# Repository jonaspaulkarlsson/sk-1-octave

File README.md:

# sk-1-octave
## Octave switch for the Casio SK-1 keyboard

## Background
The SK-1 is a great keyboard, but it's range is limited due to the short 2.5 octave keyboard.

Looking at the schematic in the service manual (http://www.burnkit2600.com/manuals/CASIO_SK-1_SRVC.pdf), the clock for the microprocessor is generated by a simple LC oscillator, like what is presented here: http://www.learningaboutelectronics.com/Articles/Colpitts-oscillator-calculator.php.

The tuning of the instrument is controlled by a variable capacitor, which controls the frequency of the LC clock oscillator. The idea is to replace the inverter in the original oscillator with a CMOS inverter IC, add a clock divider to drop the frequency by four (down two octaves) and a multiplexer to select either the original or the divided frequency.

PCB area around the micro processor and LC oscillator circuit:

Original oscillator input signal:

Original oscillator output signal:

## Circuit design
The schematic and PCB was designed in KiCad.

The schematic below shows the circuit:

The oscillator core consists of the existing inductor and capacitors from the original circuit, but now connected to one part of U1, a 4069 hex CMOS inverter. The signal from the oscillator is divided by four by two stages from U2, a dual D flip-flop. Lastly, one of the original or divided down signals are selected by one channel of U3, a quad mux. The select input of the mux is connected to a switch that selects either the original frequency when the switch is closed, or the divided down frequency when the switch is open.

The R2, R3, R4 and C1 network scales the output to roughly the same voltage range as the original clock signal. This is probably not necessary but the circuit was included just to be safe. In the end, C1 was excluded.

The PCB is shown in the picture below:

All connections are made to test points around the edges for easy soldering.

## Installation
1. Open upp the case and place both halves upside down, exposing the main PCB.
2. Mount the octave switch PCB with double sided tape, hot glue or whatever you have at hand in the position shown in the picture 
3. Cut the traces going to the processor where indicated by the red lines in the picture, and scrape off the solder resist on the one going in under the corner of the IC: 
4. Solder wires to the octave switch PCB from the solder joints on the SK-1 PCB as shown in the picture. Solder in the OUT signal with as thin a wire as possible to minimize stress on the cut wire. Take care to leave the area close to the tuning inductor free from wires. 
5. Mount a toggle swithch to some convenient place in the case, probaly the empty space next to the speaker is most convenient. Connect the switch with long twisted wires to the SW1 and SW2 pads. 
6. Put your SK-1 back together and enjoy your extended note range!

It should be noted that the SK-1 uses a weird form of negative logic, so what is connected to GND the octave switch PCB is actually the negative supply rail, and what is connected to +5V is ground. What matters in the end is that both PCBs sees signals that are in the correct voltage ranges for their respective supplies.

## Results
Audio demos at [Soundcloud](https://soundcloud.com/exterm/sk-1-octave)

The circuit works well and unlocks some of the potential of this instrument. I really like the cruncy atmospheric sound of the lower octaves.

However there are some side effects (features?) due to the nature of this hack. Since the clock speed for the whole system is slowed down, _everything_ slows down. Rythms (nice and crunchy, but slow), portamento, vibrato, envelopes etc. It doesn't bother me too much, but it should be noted that the integration is not seamless.

## Retrospective
1. I thought I ordered 1mm thick PCBs, but apparently it was the standard 1.6mm. I wanted to keep as much clearance to the case as possible, not knowing exactly how much room there was, but 1.6mm worked out fine.
2. The black solder resist fom JLCPCB was quite fragile and chipped away in one place. I will go for the standard green in the future.
3. It would have been cool to design the PCB around the solder in poisitions on the SK-1 PCB so that it could be attached directly with castellated edges. It would have been a fun exercise. Maybe for another project.
4. Yes I know the soldering looks awful, I should probably redo it, but... meh.
5. The SK-1 PCB is covered in sticky flux. I did clean it up around the area where I attached the octave switch PCB, but yeah, I know it looks nasty.

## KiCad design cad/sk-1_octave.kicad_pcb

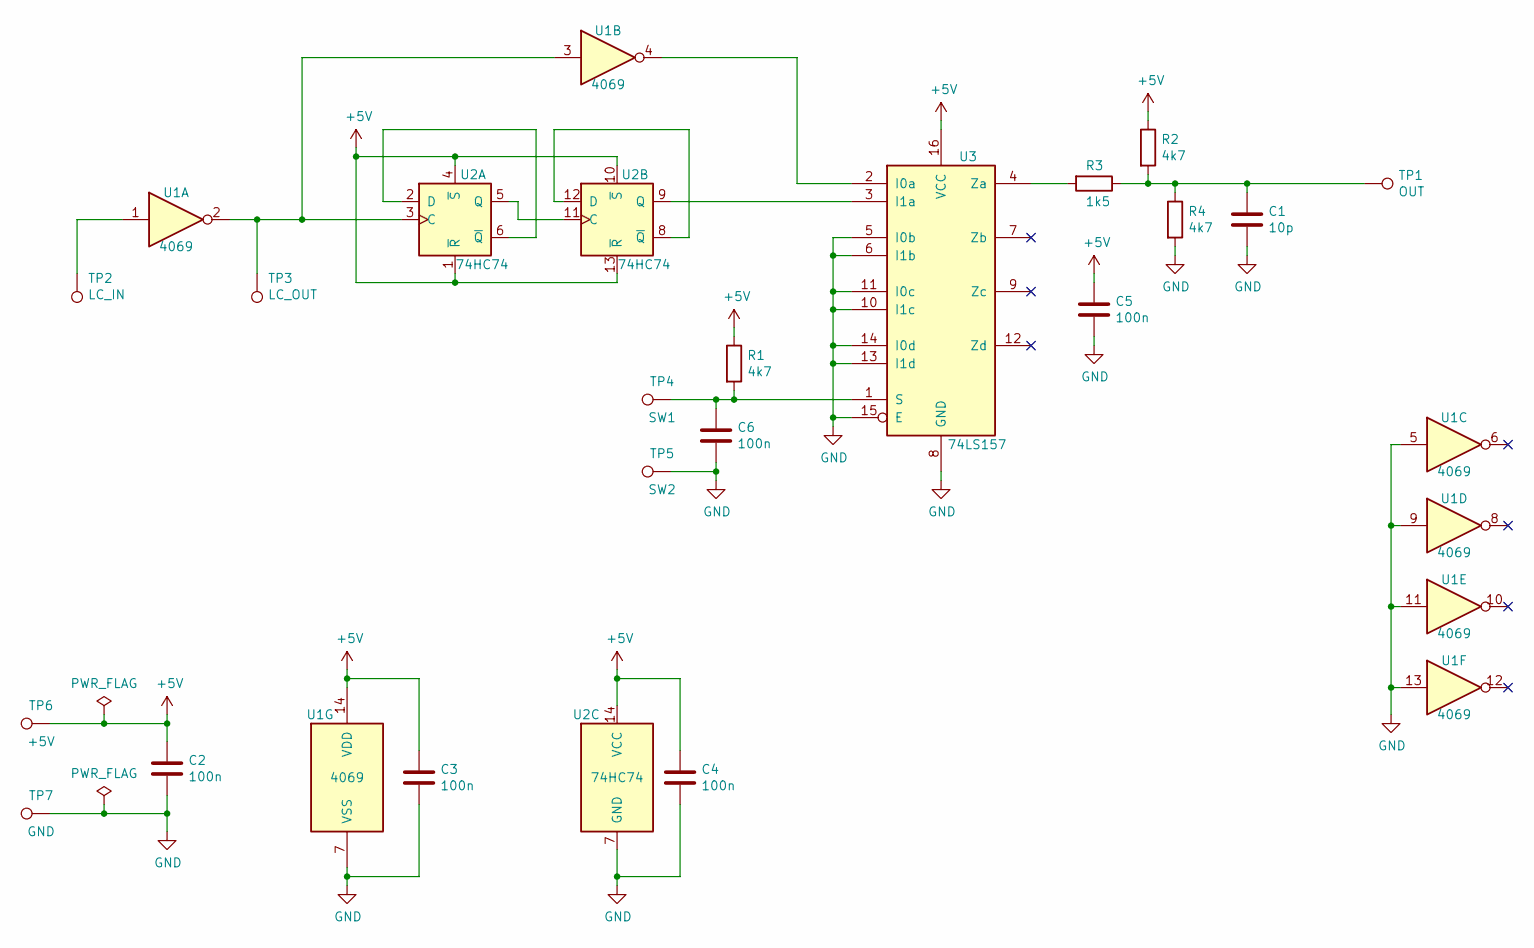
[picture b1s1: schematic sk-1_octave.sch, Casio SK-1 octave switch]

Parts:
C1: 10p; C_0603_1608Metric_Pad1.08x0.95mm_HandSolder
C2, C3, C4, C5, C6: 100n; C_0603_1608Metric_Pad1.08x0.95mm_HandSolder
R1, R2, R4: 4k7; R_0603_1608Metric_Pad0.98x0.95mm_HandSolder
R3: 1k5; R_0603_1608Metric_Pad0.98x0.95mm_HandSolder
TP1: OUT; TestPoint_Pad_D2.0mm
TP2: LC_IN; TestPoint_Pad_D2.0mm
TP3: LC_OUT; TestPoint_Pad_D2.0mm
TP4: SW1; TestPoint_Pad_D2.0mm
TP5: SW2; TestPoint_Pad_D2.0mm
TP6: +5V; TestPoint_Pad_D2.0mm
TP7: GND; TestPoint_Pad_D2.0mm
U1: 4069; SO-14_3.9x8.65mm_P1.27mm
U2: 74HC74; SO-14_3.9x8.65mm_P1.27mm
U3: 74LS157; SOIC-16_3.9x9.9mm_P1.27mm

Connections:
+5V: C2.1, C3.1, C4.1, C5.1, R1.1, R2.1, TP6.1, U1.14 (VDD), U2.1 (~R), U2.4 (~S), U2.10 (~S), U2.13 (~R), U2.14 (VCC), U3.16 (VCC)
GND: C1.2, C2.2, C3.2, C4.2, C5.2, C6.2, R4.2, TP5.1, TP7.1, U1.5, U1.7 (VSS), U1.9, U1.11, U1.13, U2.7 (GND), U3.5 (I0b), U3.6 (I1b), U3.8 (GND), U3.10 (I1c), U3.11 (I0c), U3.13 (I1d), U3.14 (I0d), U3.15 (E)
unnamed: C1.1, R2.2, R3.1, R4.1, TP1.1
unnamed: C6.1, R1.2, TP4.1, U3.1 (S)
unnamed: R3.2, U3.4 (Za)
unnamed: TP2.1, U1.1
unnamed: TP3.1, U1.2, U1.3, U2.3 (C)
unnamed: U1.4, U3.2 (I0a)
unnamed: U2.2 (D), U2.6 (~Q)
unnamed: U2.9 (Q), U3.3 (I1a)
unnamed: U2.5 (Q), U2.11 (C)
unnamed: U2.8 (~Q), U2.12 (D)

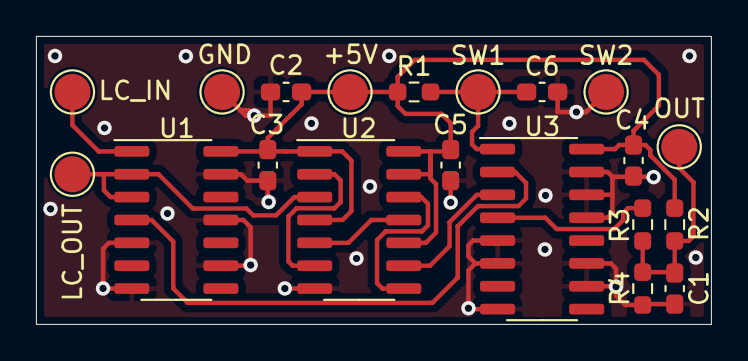
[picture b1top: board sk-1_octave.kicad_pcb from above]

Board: 2 copper layers, 37.5 x 16.0 mm, 20 parts (0 on the bottom side), 12 nets.

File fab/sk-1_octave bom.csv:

Ref,Qnty,Value,Footprint,Description
"C1, ",1,10p,0603,Ceramic capacitor
"C2, C3, C4, C5, C6, ",5,100n,0603,Ceramic capacitor
"R1, R2, R4, ",3,4k7,0603,Resistor
"R3, ",1,1k5,0603,Resistor
"U1, ",1,CD4069UBM,SOIC-14,Hex inverter
"U2, ",1,SN74HC74DR,SOIC-14,"Dual D Flip-flop, Set & Reset"
"U3, ",1,SN74HC157DR,SOIC-16,Quad 2 to 1 line Multiplexer

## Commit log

2021-03-11 PCB project files
2021-03-11 Add decription
2021-03-14 Moved CAD files to separate folder
2021-03-14 Added output signal conditioning.
2021-03-16 Minor cleanup of PCB. Generated gerbers and drill files. Created BOM.
2021-03-23 Minor tweaks to layout. Added documentation.
2021-05-01 74LSS157 -> 74HCS157. Removed backup files from versioning.
2021-05-13 Installation pictures added.
2021-06-13 74HCS157 -> 74HC157
